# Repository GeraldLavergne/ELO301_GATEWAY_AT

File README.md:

# GATEWAY_AT
Integrantes:
  - Gerald Lavergne
  - Katia Urrutia
  - Lucas Pino
  - Nicolás Jorquera

Equipo:
  - Grupo 12
  
Repositorio del proyecto GATEWAY-AT ELO301 2022-2

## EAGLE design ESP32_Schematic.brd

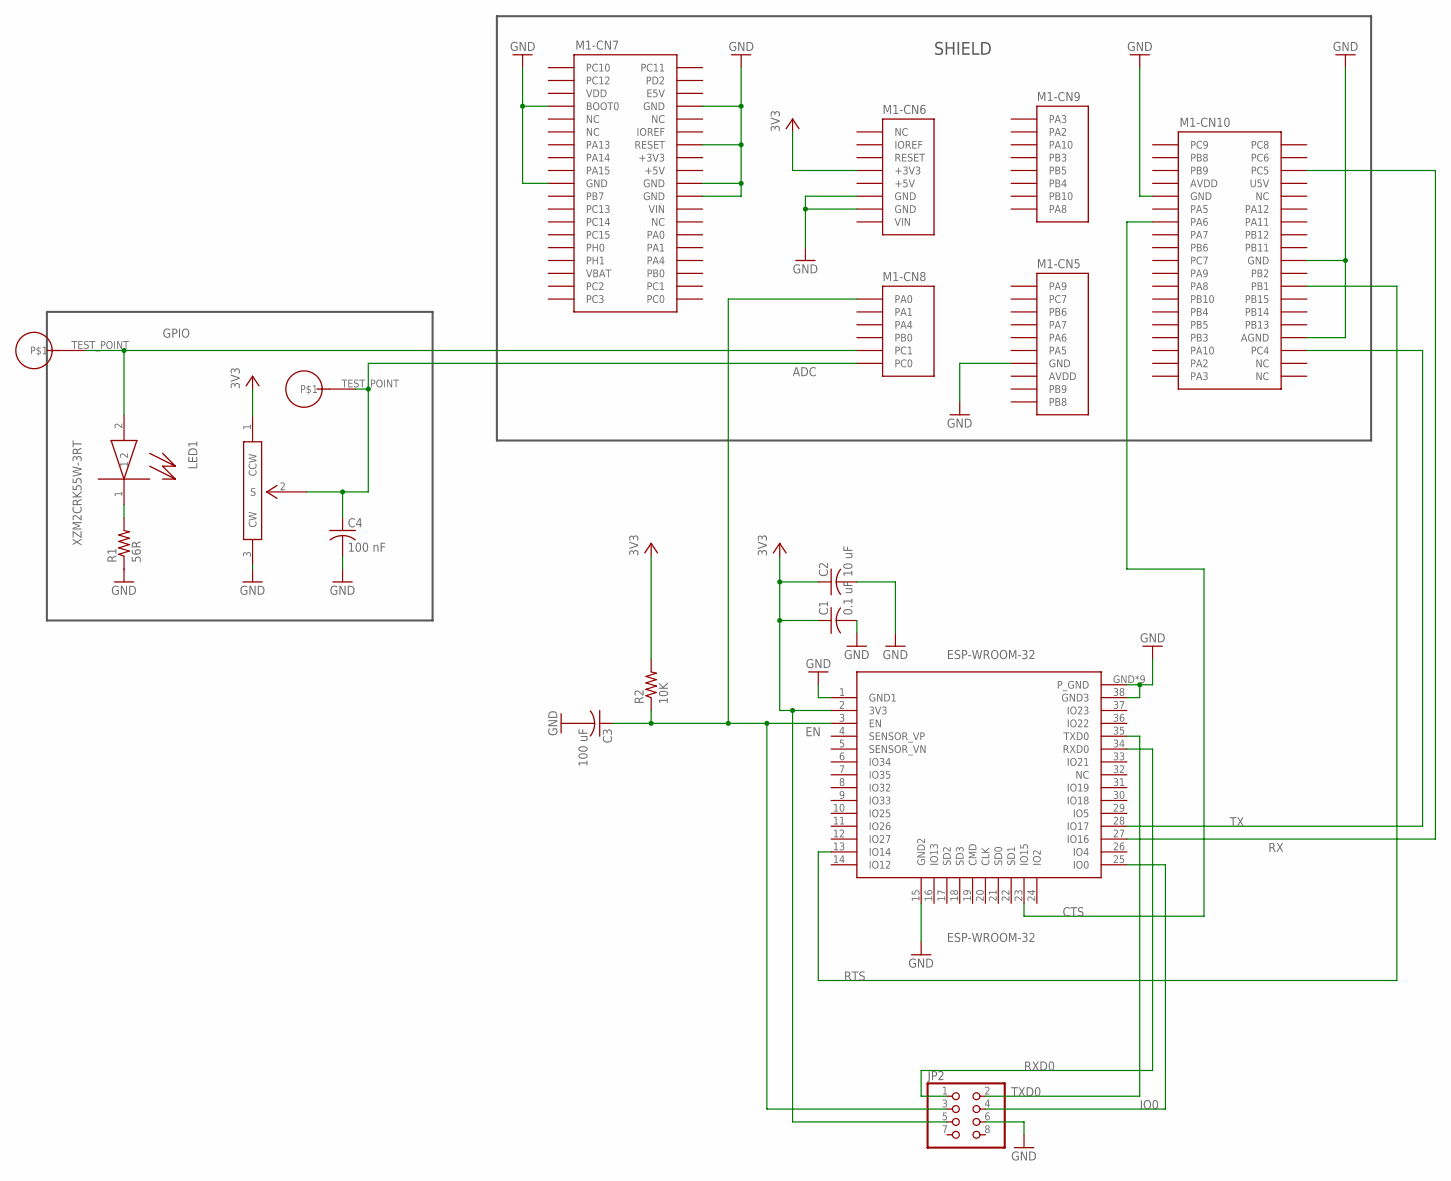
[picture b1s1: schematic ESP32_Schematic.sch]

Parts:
C1: 0.1 uF; C0805; PARTNO GCM21BR72A104KA37L
C2: 10 uF; C0805; PARTNO GRM21BR61C106KE15L
C3: 100 uF; C0805; PARTNO GRM21BR60J107ME15L
C4: 100 nF; C0805; PARTNO GCM21BR72A104KA37L
ESP-WROOM-32: ESP-WROOM-32
JP2: PINHD-2X4; 2X04; PARTNO 220-1-08-003
LED1: XZM2CRK55W-3RT; CHIPLED; PARTNO XZM2CRK55W-3RT
M1: NUCLEO-L452RE; NUCLEO-64
POT1: P160KNP; P160KN-0QD15B10K
R1: 56R; R0805; PARTNO RC0805JR-0756RL
R2: 10K; R0805; PARTNO RC0805FR-0710KL
TP_LED: TEST_POINT
TP_POT: TEST_POINT

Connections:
+3V3: M1.CN7-16 (+3V3)
+5V: M1.CN6-5 (+5V), M1.CN7-18 (+5V)
ADC: C4.1, M1.CN8-6 (PC0), POT1.2 (S), TP_POT.TEST_POINT
AVDD: M1.CN5-8 (AVDD), M1.CN10-7 (AVDD)
CTS: ESP-WROOM-32.23 (IO15), M1.CN10-13 (PA6)
EN: C3.1, ESP-WROOM-32.3 (EN), JP2.3, M1.CN8-1 (PA0), R2.1
GND: C1.2, C2.2, C3.2, C4.2, ESP-WROOM-32.1 (GND1), ESP-WROOM-32.15 (GND2), ESP-WROOM-32.38 (GND3), ESP-WROOM-32.GND (P_GND), ESP-WROOM-32.GND1 (P_GND), ESP-WROOM-32.GND2 (P_GND), ESP-WROOM-32.GND3 (P_GND), ESP-WROOM-32.GND4 (P_GND), ESP-WROOM-32.GND5 (P_GND), ESP-WROOM-32.GND6 (P_GND), ESP-WROOM-32.GND7 (P_GND), ESP-WROOM-32.GND8 (P_GND), JP2.6, M1.CN5-7 (GND), M1.CN6-6 (GND), M1.CN6-7 (GND), M1.CN7-7 (BOOT0), M1.CN7-8 (GND), M1.CN7-14 (RESET), M1.CN7-19 (GND), M1.CN7-20 (GND), M1.CN7-22 (GND), M1.CN10-9 (GND), M1.CN10-20 (GND), M1.CN10-32 (AGND), POT1.3 (CW), R1.1
GPIO: LED1.2, M1.CN8-5 (PC1), TP_LED.TEST_POINT
IO0: ESP-WROOM-32.25 (IO0), JP2.4
IOREF: M1.CN6-2 (IOREF)
unnamed: LED1.1, R1.2
RTS: ESP-WROOM-32.13 (IO14), M1.CN10-24 (PB1)
RX: ESP-WROOM-32.27 (IO16), M1.CN10-6 (PC5)
RXD0: ESP-WROOM-32.34 (RXD0), JP2.1
TX: ESP-WROOM-32.28 (IO17), M1.CN10-34 (PC4)
TXD0: ESP-WROOM-32.35 (TXD0), JP2.2
U5V: M1.CN10-8 (U5V)
VBAT: M1.CN7-33 (VBAT)
VCC: C1.1, C2.1, ESP-WROOM-32.2 (3V3), JP2.5, M1.CN6-4 (+3V3), POT1.1 (CCW), R2.2
VDD: M1.CN7-5 (VDD)
VIN: M1.CN6-8 (VIN), M1.CN7-24 (VIN)

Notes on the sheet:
SHIELD

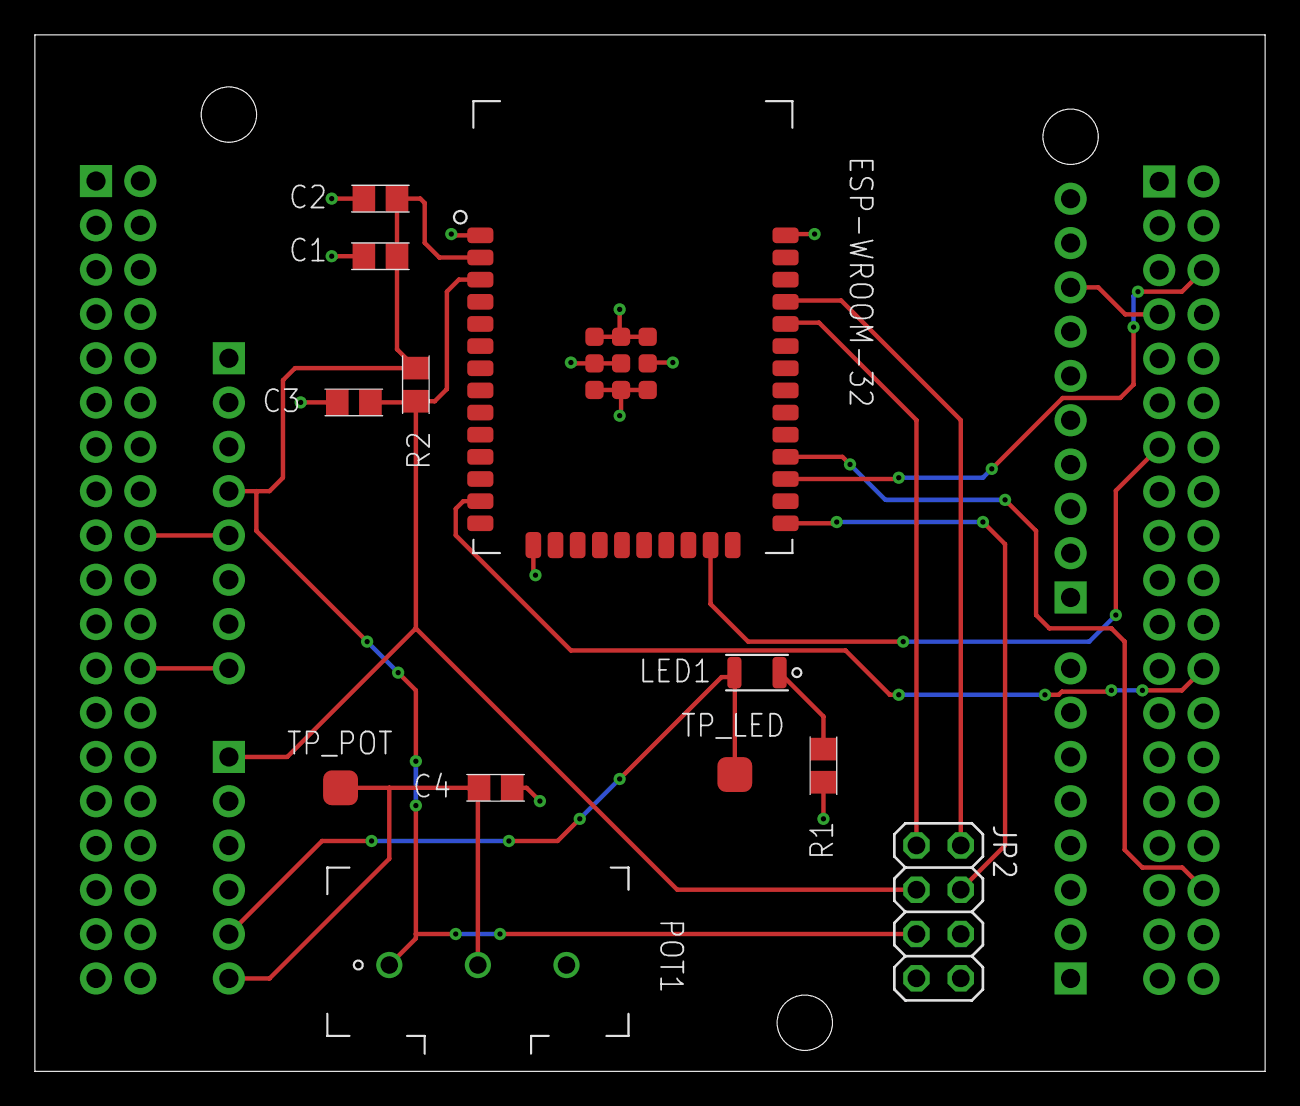
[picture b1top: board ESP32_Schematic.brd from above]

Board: 2 copper layers, 70.5 x 59.4 mm, 13 parts (0 on the bottom side), 16 nets.

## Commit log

2022-11-16 Se agrega el proyecto
2022-11-17 Se modifican unas librerias y se agregan archivos finales
2022-11-17 Ultimas modificaciones
2022-11-17 Se añade BOM en xlsx
2022-11-17 Create README.md
    Se añade README (Otra vez)
